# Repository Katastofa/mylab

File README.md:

# school21

- [`hardware/`](hardware/README.md) — разработка плат: схема кодом на SKiDL, разводка в KiCad.

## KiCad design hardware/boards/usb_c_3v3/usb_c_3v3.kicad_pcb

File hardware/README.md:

# Платы: SKiDL + KiCad

Схема пишется кодом на Python ([SKiDL](https://github.com/devbisme/skidl)),
а KiCad используется для разводки платы и выпуска файлов на производство.

```
boards/<плата>/<плата>.py ──SKiDL──▶ build/<плата>.net ──импорт──▶ <плата>.kicad_pcb ──▶ gerbers
          (источник правды)     │      (netlist)                      (разводка руками)
                                └──▶ build/sch/*.kicad_sch  (схема только для просмотра)
```

Что лежит в git:

| Файл                    | Кто правит        | Зачем                                   |
|-------------------------|-------------------|-----------------------------------------|
| `boards/*/*.py`         | человек           | схема: компоненты, цепи, футпринты      |
| `lib/blocks.py`         | человек           | переиспользуемые блоки (`@subcircuit`)  |
| `boards/*/*.kicad_pcb`  | человек, в KiCad  | расстановка и трассировка               |
| `boards/*/*.kicad_pro`  | KiCad             | настройки проекта (правила DRC и т. п.) |
| `build/`                | генерируется      | netlist, схема, gerbers — не коммитим   |

## Установка

1. KiCad 9 (подойдёт и 8): https://www.kicad.org/download/
2. Python-зависимости:
   ```sh
   cd hardware
   python3 -m venv .venv && . .venv/bin/activate   # Windows: .venv\Scripts\activate
   pip install -r requirements.txt
   ```
3. Библиотеки символов KiCad ищутся автоматически (`lib/kicad_env.py`).
   Если не нашлись — укажите путь вручную:
   ```sh
   export KICAD9_SYMBOL_DIR="/path/to/kicad/symbols"
   ```
   Для другой версии KiCad: `export SKIDL_KICAD=8`.

## Цикл работы

1. **Правим схему** в `boards/<плата>/<плата>.py`.
2. **Собираем**:
   ```sh
   cd boards/usb_c_3v3
   python usb_c_3v3.py --sch
   ```
   Запускается ERC (при ошибках netlist не создаётся), затем пишутся
   `build/usb_c_3v3.net` и схема `build/sch/usb_c_3v3.kicad_sch`.
3. **Обновляем плату**: открываем `usb_c_3v3.kicad_pro` → PCB Editor →
   `File → Import → Netlist…` → выбираем `build/usb_c_3v3.net` →
   *Link footprints using: Symbol UUIDs* (по умолчанию) → `Update PCB`.
   Новые компоненты появятся рядом с платой, удалённые пропадут,
   расставленные останутся на месте.
4. **Разводим** в KiCad, проверяем DRC, коммитим `.py` и `.kicad_pcb` вместе.
5. **Производство**: `make fab` (или артефакт CI) → `build/fab/` с gerbers,
   сверловкой, файлом расстановки и DRC-отчётом.

Сгенерированную схему не редактируем: при следующей сборке она перезапишется.
Она нужна, чтобы глазами проверить связи и приложить PDF к ревью.

### Почему расстановка не слетает

У каждого блока и компонента есть `tag`. Из цепочки тегов
(`usb/r_cc1`, `ldo/c_out`…) SKiDL строит стабильный UUID, и KiCad сопоставляет
футпринты по нему, а не по позиционному обозначению. Поэтому:

- теги задаём всегда и не меняем без нужды — смена тега = «новый» компонент;
- R1/C3 могут перенумероваться — это нормально.

## Новая плата

```sh
mkdir boards/my_board
cp boards/usb_c_3v3/usb_c_3v3.py boards/my_board/my_board.py
```

Правим схему, собираем, затем в KiCad: `File → New Project` в
`boards/my_board/` с именем `my_board`, открываем PCB Editor, рисуем контур
на слое `Edge.Cuts` и импортируем netlist (шаг 3).

## Как писать схему

```python
from skidl import Net, Part, subcircuit

@subcircuit
def indicator_led(vcc, gnd, r_value="1k", color="green"):
    led = Part("Device", "LED", value=color,
               footprint="LED_SMD:LED_0603_1608Metric", tag="led")
    vcc & resistor(r_value, tag="r") & led["A K"] & gnd   # последовательная цепочка

indicator_led(v3v3, gnd, tag="pwr_led")
```

- `Part("Библиотека", "Символ", footprint="Библиотека:Футпринт")` — имена те же,
  что в KiCad (Symbol Editor / Footprint Editor).
- `net += part["PIN"]` — подключить вывод к цепи; `a & b & c` — последовательно.
- Пины можно звать по имени (`"VO"`) или номеру (`1`).
- Посмотреть выводы символа:
  `python -c "import sys; sys.path.insert(0,'lib'); import kicad_env; from skidl import *; print(Part('Regulator_Linear','AMS1117-3.3',dest=TEMPLATE))"`

## CI

`.github/workflows/hardware.yml` на каждый push в `hardware/` собирает все
платы в контейнере `kicad/kicad:9.0`: ERC, netlist, схема (PDF), DRC-отчёт,
gerbers. Всё это лежит в артефакте `hardware-build` у прогона.
DRC пока не валит сборку (пример ещё не разведён) — когда плата будет готова,
уберите `|| true` у `pcb drc` в `Makefile` и добавьте `--exit-code-violations`.

## Пример: `boards/usb_c_3v3`

USB-C (только питание, 5 В) → AMS1117-3.3 → 3.3 В, светодиод питания,
гребёнка `+5V / +3V3 / GND / GND`. Футпринты расставлены, контур 36×22 мм
нарисован — осталось развести дорожки.

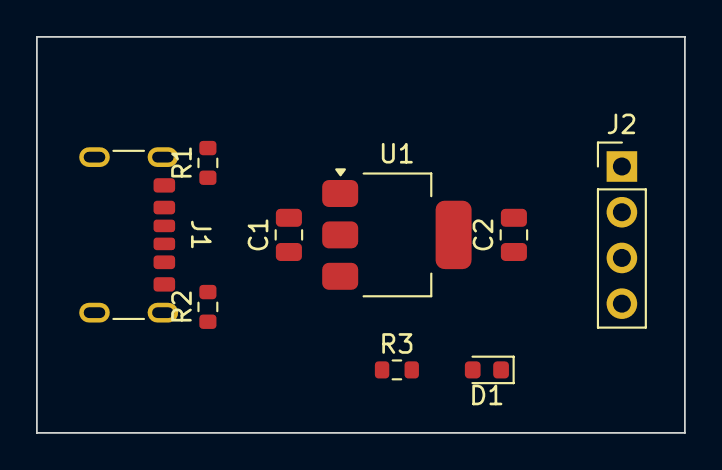
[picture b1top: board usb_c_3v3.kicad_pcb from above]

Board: 2 copper layers, 36.0 x 22.0 mm, 9 parts (0 on the bottom side), 6 nets, no tracks yet.

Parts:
C1: 10u; C_0805_2012Metric
C2: 22u; C_0805_2012Metric
D1: green; LED_0603_1608Metric
J1: USB_C_Receptacle_PowerOnly_6P; USB_C_Receptacle_GCT_USB4125-xx-x_6P_TopMnt_Horizontal
J2: Conn_01x04; PinHeader_1x04_P2.54mm_Vertical
R1, R2: 5.1k; R_0603_1608Metric
R3: 1k; R_0603_1608Metric
U1: AMS1117-3.3; SOT-223-3_TabPin2

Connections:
+3V3: C2.1, J2.2, R3.1, U1.2
+5V: C1.1, J1.A9, J1.B9, J2.1, U1.3
GND: C1.2, C2.2, D1.1, J1.A12, J1.B12, J1.S1, J2.3, J2.4, R1.2, R2.2, U1.1
unnamed: J1.A5, R1.1
unnamed: J1.B5, R2.1
unnamed: D1.2, R3.2

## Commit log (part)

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2026-05-19 first
